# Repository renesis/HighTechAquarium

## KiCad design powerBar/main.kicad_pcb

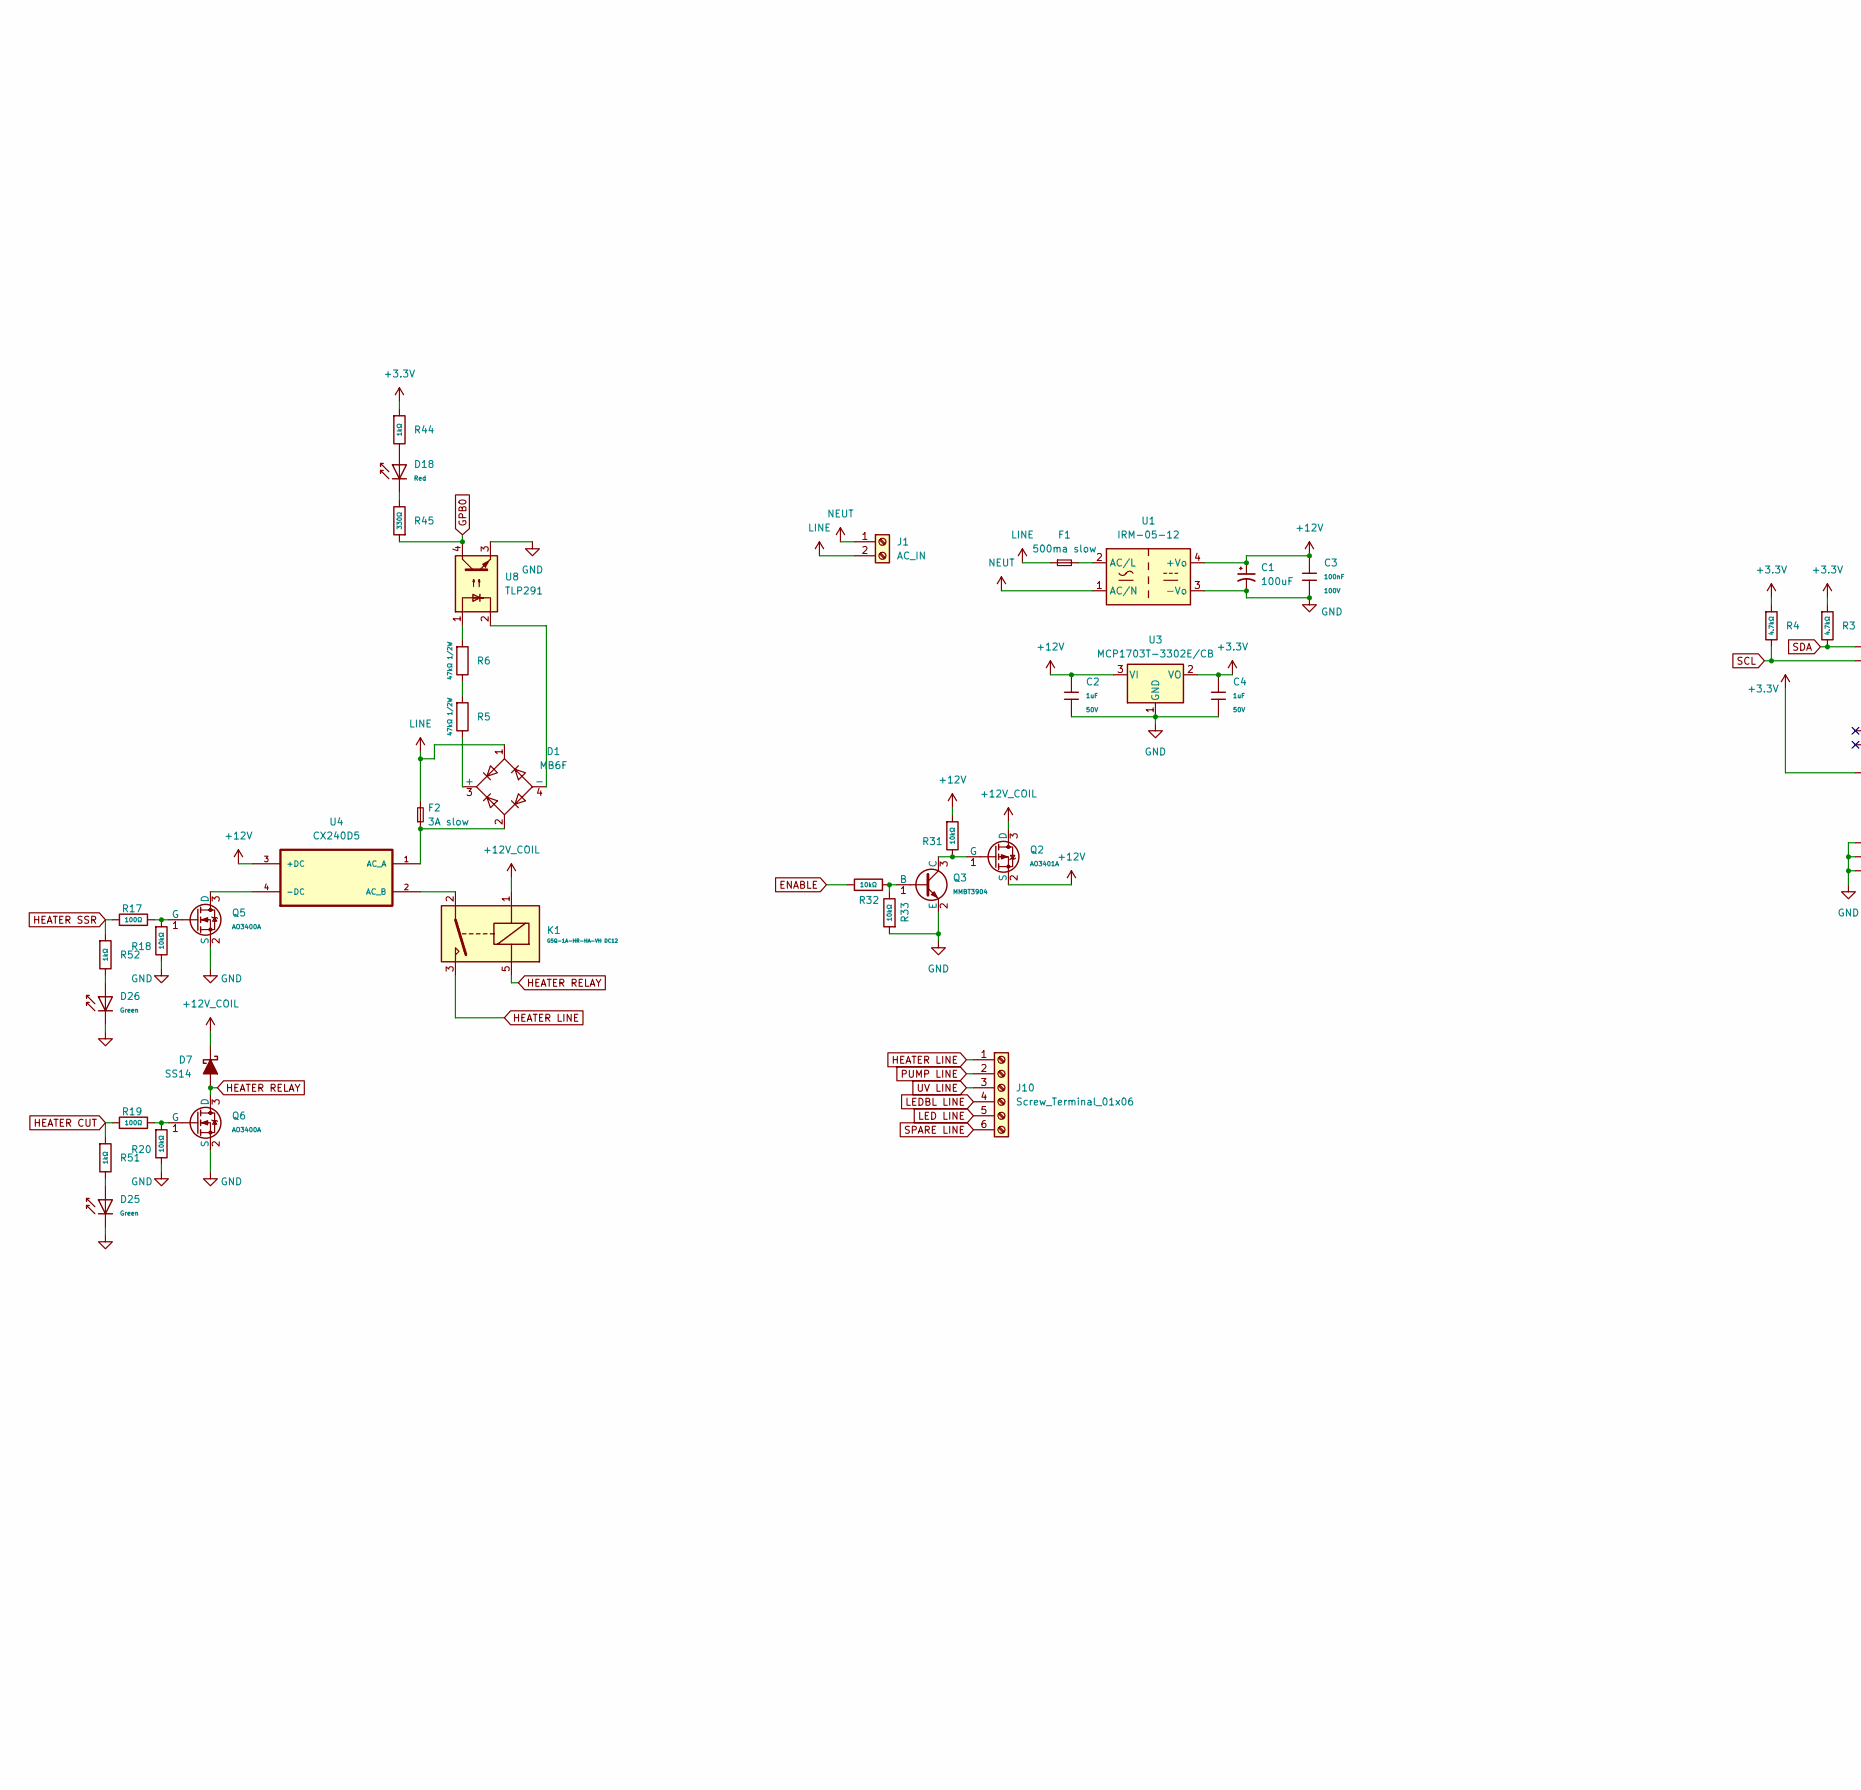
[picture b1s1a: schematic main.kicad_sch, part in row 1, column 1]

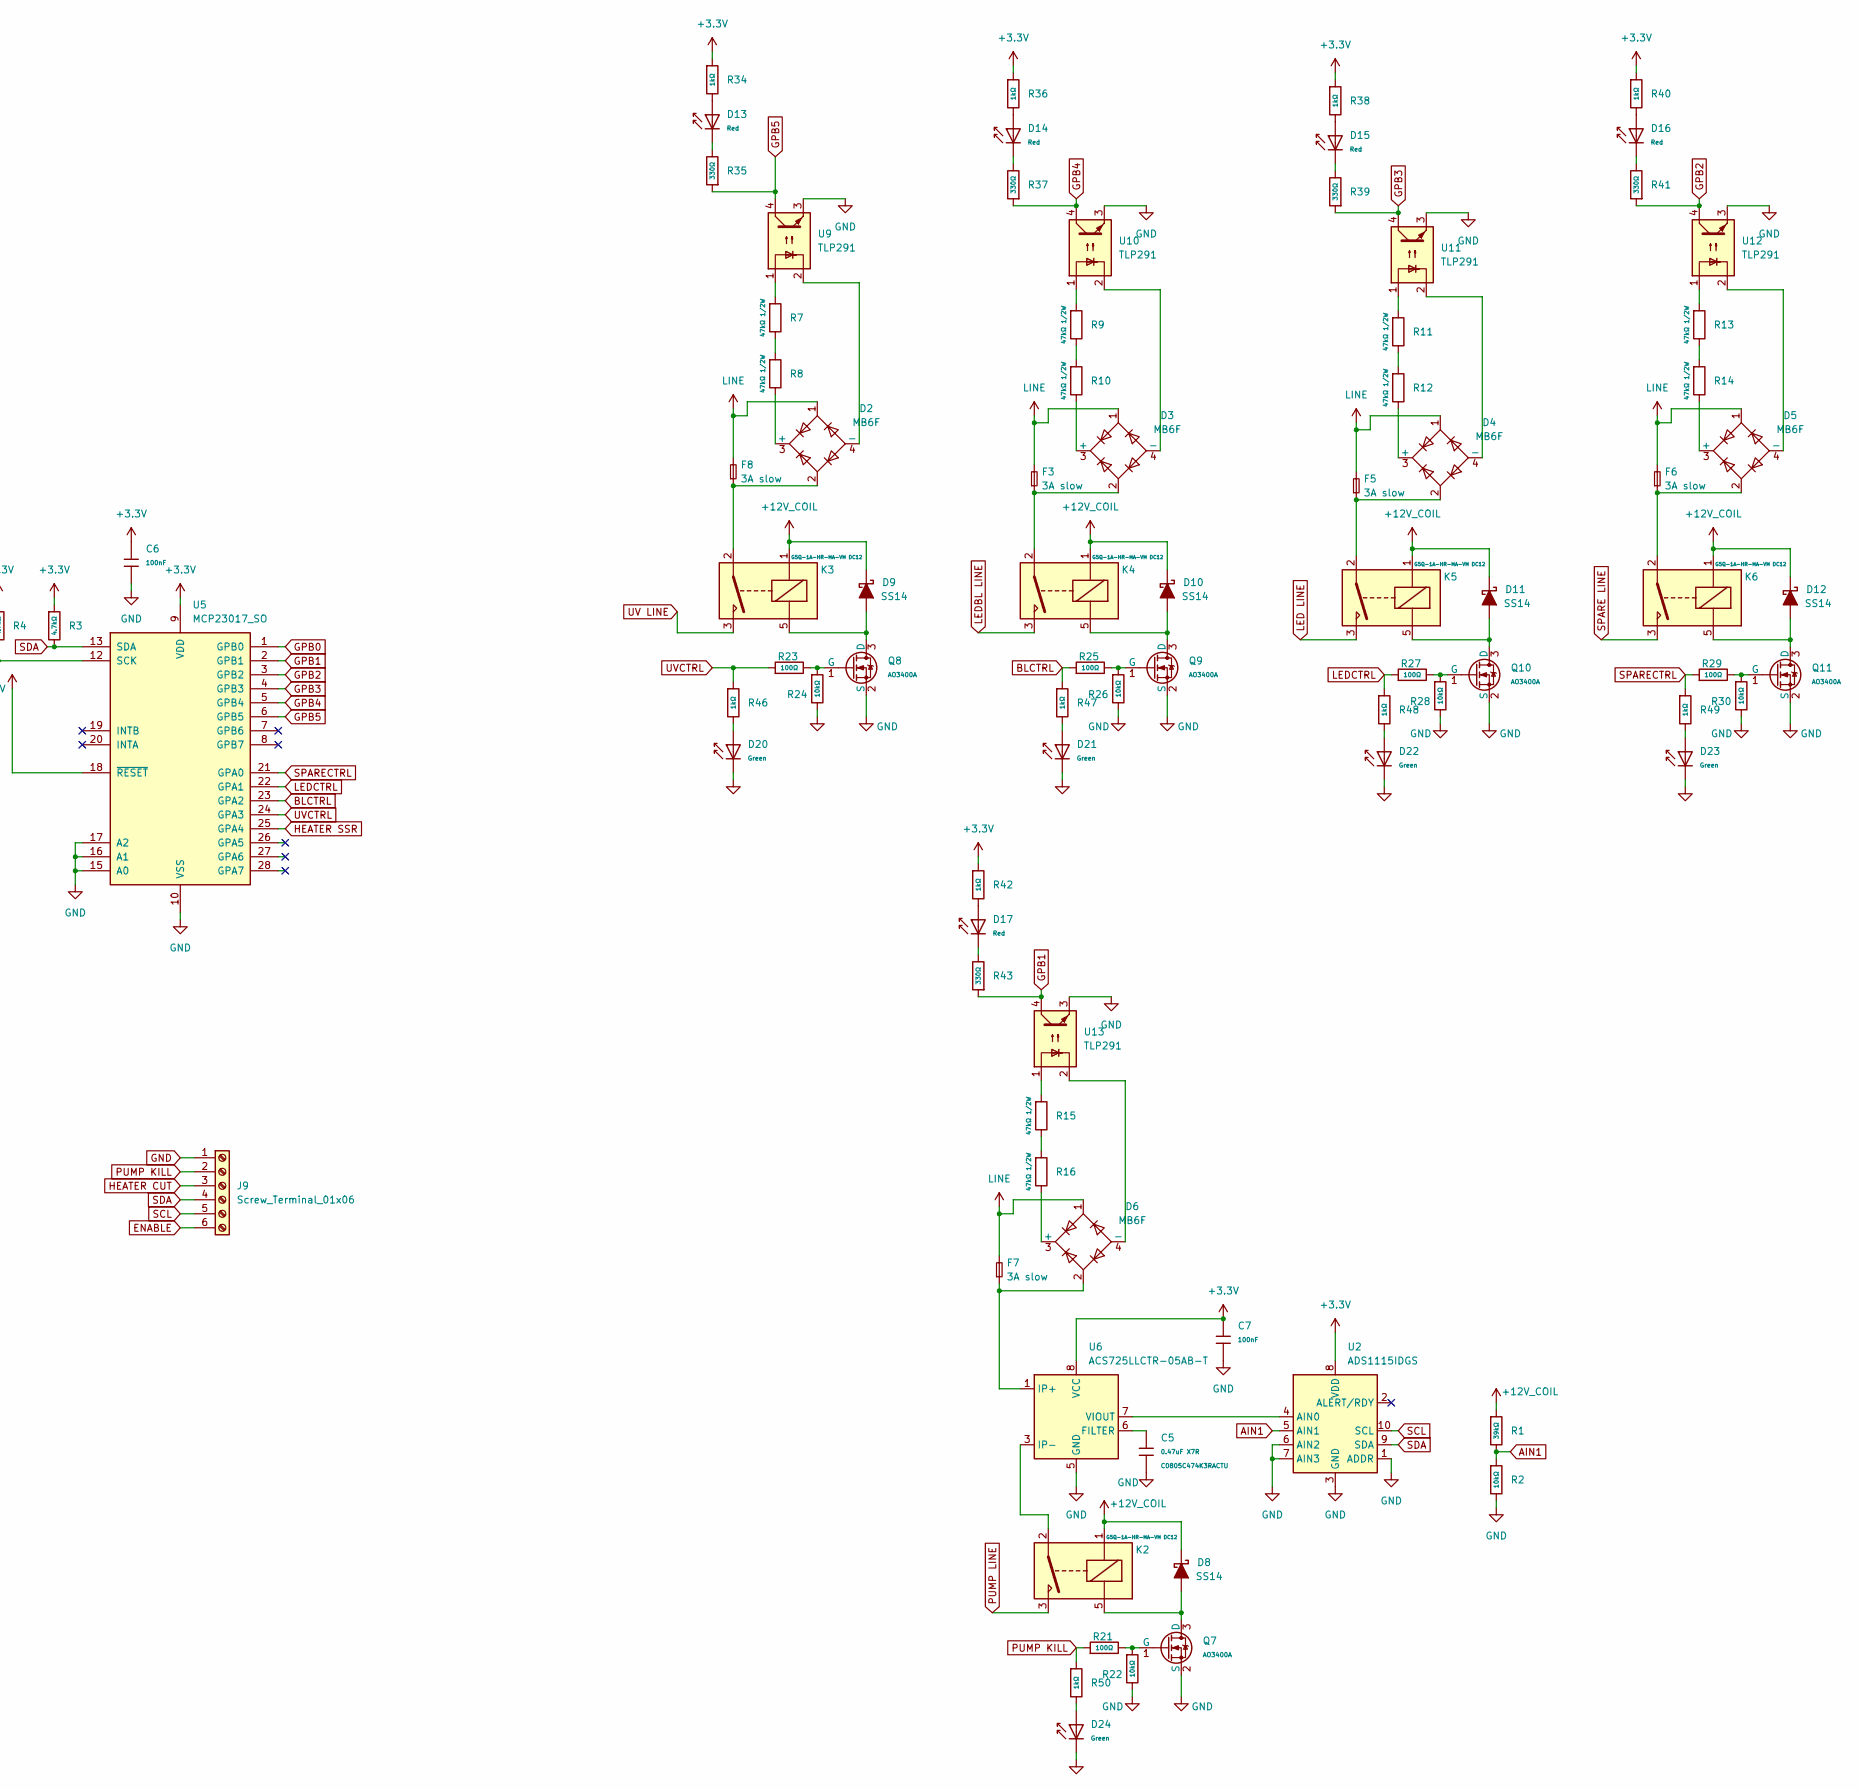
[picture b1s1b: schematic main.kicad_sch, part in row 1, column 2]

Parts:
C1: 100uF; C_Radial_D6.3mm_H11.0mm_P2.50mm
C2, C4: 1uF; C_0805; Voltage Rated 50V; Tolerance ±10%; Part CL21B105KBFNNNE; LCSC C28323
C3: 100nF; C_0805; Voltage Rated 100V; Tolerance ±10%; Part CL21B104KCFNNNE; LCSC C28233
C5: 0.47uF X7R; C_0805; Voltage Rated C0805C474K3RACTU; Tolerance ±10%; Part CL21B105KBFNNNE
C6, C7: 100nF; C_0805; Voltage Rated 50V; Tolerance ±10%; Part CC0805KRX7R9BB104; LCSC C49678
D1, D2, D3, D4, D5, D6: MB6F; TO-269AA
D7, D8, D9, D10, D11, D12: SS14; D_SMA
D13, D14, D15, D16, D17, D18: Red; D_0805; Forward Voltage (VF) 1.6V~2.6V; Part NCD0805R1; LCSC C84256
D20, D21, D22, D23, D24, D25, D26: Green; D_0805; Part KT-0805G; LCSC C2297
F1: 500ma slow; Fuseholder_Blade_Mini_Keystone_3568
F2, F3, F5, F6, F7, F8: 3A slow; Fuseholder_Blade_Mini_Keystone_3568
J1: AC_IN; TerminalBlock_CUI_TB007-508-02_1x02_P5.08mm_Horizontal
J9, J10: Screw_Terminal_01x06; TerminalBlock_CUI_TB007-508-06_1x06_P5.08mm_Horizontal
K1, K2, K3, K4, K5, K6: G5Q-1A-HR-HA-VH DC12; Relay_SPST_Omron-G5Q-1A
Q2: AO3401A; Q_SOT-23; Part AO3401A; LCSC C15127
Q3: MMBT3904; Q_SOT-23; Part MMBT3904; LCSC C7420353
Q5, Q6, Q7, Q8, Q9, Q10, Q11: AO3400A; Q_SOT-23; Part AO3400A; LCSC C20917
R1: 39kΩ; R_0805; Overload Voltage (Max) 150V; Tolerance ±1%; Part 0805W8F3902T5E; LCSC C25826
R2, R18, R20, R22, R24, R26, R28, R30, R31, R32, R33: 10kΩ; R_0805; Overload Voltage (Max) 150V; Tolerance ±1%; Part 0805W8F1002T5E; LCSC C17414
R3, R4: 4.7kΩ; R_0805; Overload Voltage (Max) 150V; Tolerance ±1%; Part 0805W8F4701T5E; LCSC C17673
R5, R6, R7, R8, R9, R10, R11, R12, R13, R14, R15, R16: 47kΩ 1/2W; R_0805; Overload Voltage (Max) 150V; Tolerance ±1%; Part 0805W8F4702T5E
R17, R19, R21, R23, R25, R27, R29: 100Ω; R_0805; Overload Voltage (Max) 150V; Tolerance ±1%; Part 0805W8F1000T5E; LCSC C17408
R34, R36, R38, R40, R42, R44, R46, R47, R48, R49, R50, R51, R52: 1kΩ; R_0805; Overload Voltage (Max) 150V; Tolerance ±1%; Part 0805W8F1001T5E; LCSC C17513
R35, R37, R39, R41, R43, R45: 330Ω; R_0805; Overload Voltage (Max) 150V; Tolerance ±1%; Part 0805W8F3300T5E; LCSC C17630
U1: IRM-05-12; Converter_ACDC_MeanWell_IRM-05-xx_THT
U2: ADS1115IDGS; TSSOP-10_3x3mm_P0.5mm
U3: MCP1703T-3302E/CB; SOT-23
U4: CX240D5; CRYDOM_CX240D5
U5: MCP23017_SO; SOIC-28W_7.5x17.9mm_P1.27mm
U6: ACS725LLCTR-05AB-T; SOIC-8_3.9x4.9mm_P1.27mm
U8, U9, U10, U11, U12, U13: TLP291; SOIC-4_4.55x2.6mm_P1.27mm

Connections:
+3.3V: C4.1, C6.1, C7.1, R3.1, R4.1, R34.1, R36.1, R38.1, R40.1, R42.1, R44.1, U2.8 (VDD), U3.2 (VO), U5.9 (VDD), U5.18 (~RESET), U6.8 (VCC)
+12V: C1.1, C2.1, C3.1, Q2.2 (S), R31.1, U1.4 (+Vo), U3.3 (VI), U4.3 (+DC)
+12V_COIL: D7.1 (K), D8.1 (K), D9.1 (K), D10.1 (K), D11.1 (K), D12.1 (K), K1.1, K2.1, K3.1, K4.1, K5.1, K6.1, Q2.3 (D), R1.1
AIN1: R1.2, R2.1, U2.5 (AIN1)
BLCTRL: R25.1, R47.1, U5.23 (GPA2)
ENABLE: J9.6, R32.1
GND: C1.2, C2.2, C3.2, C4.2, C5.2, C6.2, C7.2, D20.1, D21.1, D22.1, D23.1, D24.1, D25.1, D26.1, J9.1, Q3.2 (E), Q5.2 (S), Q6.2 (S), Q7.2 (S), Q8.2 (S), Q9.2 (S), Q10.2 (S), Q11.2 (S), R2.2, R18.2, R20.2, R22.2, R24.2, R26.2, R28.2, R30.2, R33.1, U1.3 (-Vo), U2.1 (ADDR), U2.3 (GND), U2.6 (AIN2), U2.7 (AIN3), U3.1 (GND), U5.10 (VSS), U5.15 (A0), U5.16 (A1), U5.17 (A2), U6.5 (GND), U8.3, U9.3, U10.3, U11.3, U12.3, U13.3
GPB0: R45.1, U5.1 (GPB0), U8.4
GPB1: R43.1, U5.2 (GPB1), U13.4
GPB2: R41.1, U5.3 (GPB2), U12.4
GPB3: R39.1, U5.4 (GPB3), U11.4
GPB4: R37.1, U5.5 (GPB4), U10.4
GPB5: R35.1, U5.6 (GPB5), U9.4
HEATER CUT: J9.3, R19.1, R51.1
HEATER LINE: J10.1, K1.3
HEATER RELAY: D7.2 (A), K1.5, Q6.3 (D)
HEATER SSR: R17.1, R52.1, U5.25 (GPA4)
LED LINE: J10.5, K5.3
LEDBL LINE: J10.4, K4.3
LEDCTRL: R27.1, R48.1, U5.22 (GPA1)
LINE: D1.1, D2.1, D3.1, D4.1, D5.1, D6.1, F1.1, F2.2, F3.2, F5.2, F6.2, F7.2, F8.2, J1.2
NEUT: J1.1, U1.1 (AC/N)
unnamed: D1.3 (+), R5.2
unnamed: D1.4 (-), U8.2
unnamed: D2.3 (+), R8.2
unnamed: D2.4 (-), U9.2
unnamed: D2.2, F8.1, K3.2
unnamed: D3.3 (+), R10.2
unnamed: D3.4 (-), U10.2
unnamed: D3.2, F3.1, K4.2
unnamed: D4.3 (+), R12.2
unnamed: D4.4 (-), U11.2
unnamed: D4.2, F5.1, K5.2
unnamed: D5.3 (+), R14.2
unnamed: D5.4 (-), U12.2
unnamed: D5.2, F6.1, K6.2
unnamed: D6.3 (+), R16.2
unnamed: D6.4 (-), U13.2
unnamed: D6.2, F7.1, U6.1 (IP+), U6.2 (IP+)
unnamed: D8.2 (A), K2.5, Q7.3 (D)
unnamed: D9.2 (A), K3.5, Q8.3 (D)
unnamed: D10.2 (A), K4.5, Q9.3 (D)
unnamed: D11.2 (A), K5.5, Q10.3 (D)
unnamed: D12.2 (A), K6.5, Q11.3 (D)
unnamed: D13.1, R35.2
unnamed: D13.2, R34.2
unnamed: D14.1, R37.2
unnamed: D14.2, R36.2
unnamed: D15.1, R39.2
unnamed: D15.2, R38.2
unnamed: D16.1, R41.2
unnamed: D16.2, R40.2
unnamed: D17.1, R43.2
unnamed: D17.2, R42.2
unnamed: D18.1, R45.2
unnamed: D18.2, R44.2
unnamed: D20.2, R46.2
unnamed: D21.2, R47.2
unnamed: D22.2, R48.2
unnamed: D23.2, R49.2
unnamed: D24.2, R50.2
unnamed: D25.2, R51.2
unnamed: D26.2, R52.2
unnamed: K2.2, U6.3 (IP-), U6.4 (IP-)
unnamed: Q2.1 (G), Q3.3 (C), R31.2
unnamed: Q3.1 (B), R32.2, R33.2
unnamed: Q5.3 (D), U4.4 (-DC)
unnamed: Q5.1 (G), R17.2, R18.1
unnamed: Q6.1 (G), R19.2, R20.1
unnamed: Q7.1 (G), R21.2, R22.1
unnamed: Q8.1 (G), R23.2, R24.1
unnamed: Q9.1 (G), R25.2, R26.1
unnamed: Q10.1 (G), R27.2, R28.1
unnamed: Q11.1 (G), R29.2, R30.1
unnamed: R5.1, R6.2
unnamed: R6.1, U8.1
unnamed: R7.1, U9.1
unnamed: R7.2, R8.1
unnamed: R9.1, U10.1
unnamed: R9.2, R10.1
unnamed: R11.1, U11.1
unnamed: R11.2, R12.1
unnamed: R13.1, U12.1
unnamed: R13.2, R14.1
unnamed: R15.1, U13.1
unnamed: R15.2, R16.1
unnamed: F1.2, U1.2 (AC/L)
unnamed: U2.4 (AIN0), U6.7 (VIOUT)
unnamed: D1.2, F2.1, U4.1 (AC_A)
unnamed: K1.2, U4.2 (AC_B)
unnamed: C5.1, U6.6 (FILTER)
PUMP KILL: J9.2, R21.1, R50.1
PUMP LINE: J10.2, K2.3
SCL: J9.5, R4.2, U2.10 (SCL), U5.12 (SCK)
SDA: J9.4, R3.2, U2.9 (SDA), U5.13 (SDA)
SPARE LINE: J10.6, K6.3
SPARECTRL: R29.1, R49.1, U5.21 (GPA0)
UV LINE: J10.3, K3.3
UVCTRL: R23.1, R46.1, U5.24 (GPA3)

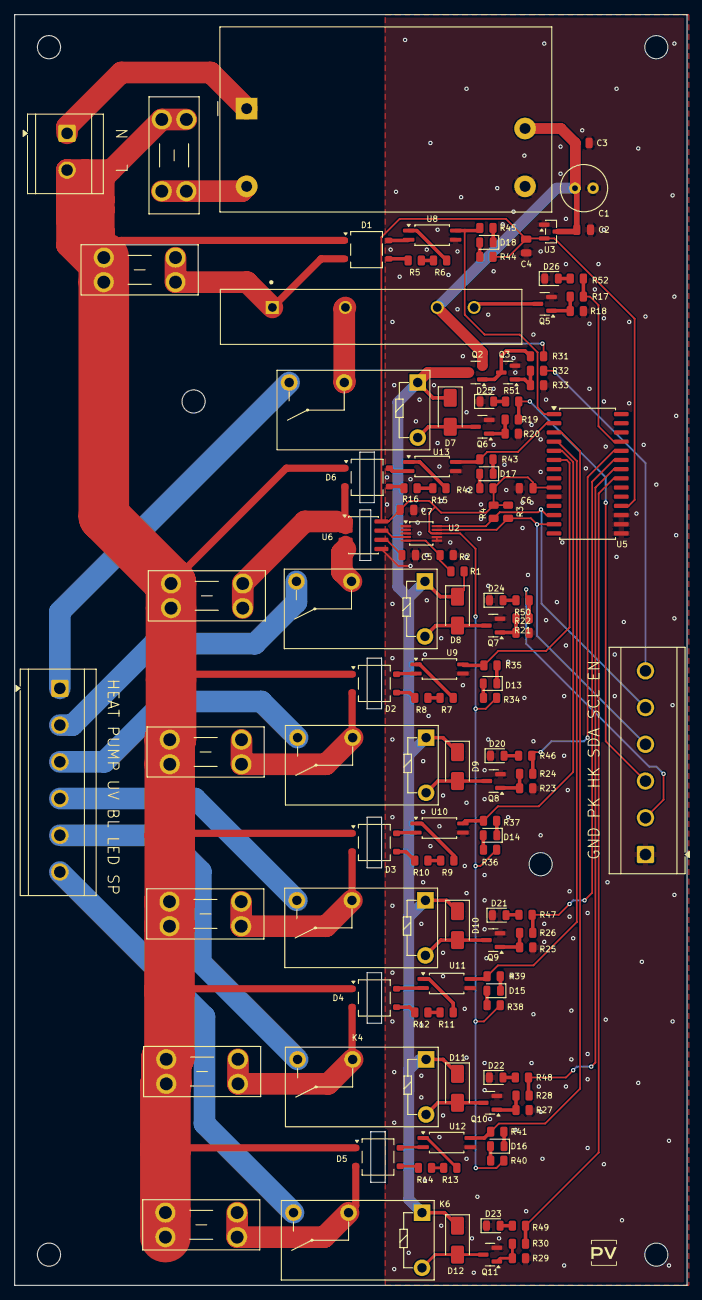
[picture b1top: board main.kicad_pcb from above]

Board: 2 copper layers, 93.0 x 175.8 mm, 121 parts (0 on the bottom side), 99 nets.

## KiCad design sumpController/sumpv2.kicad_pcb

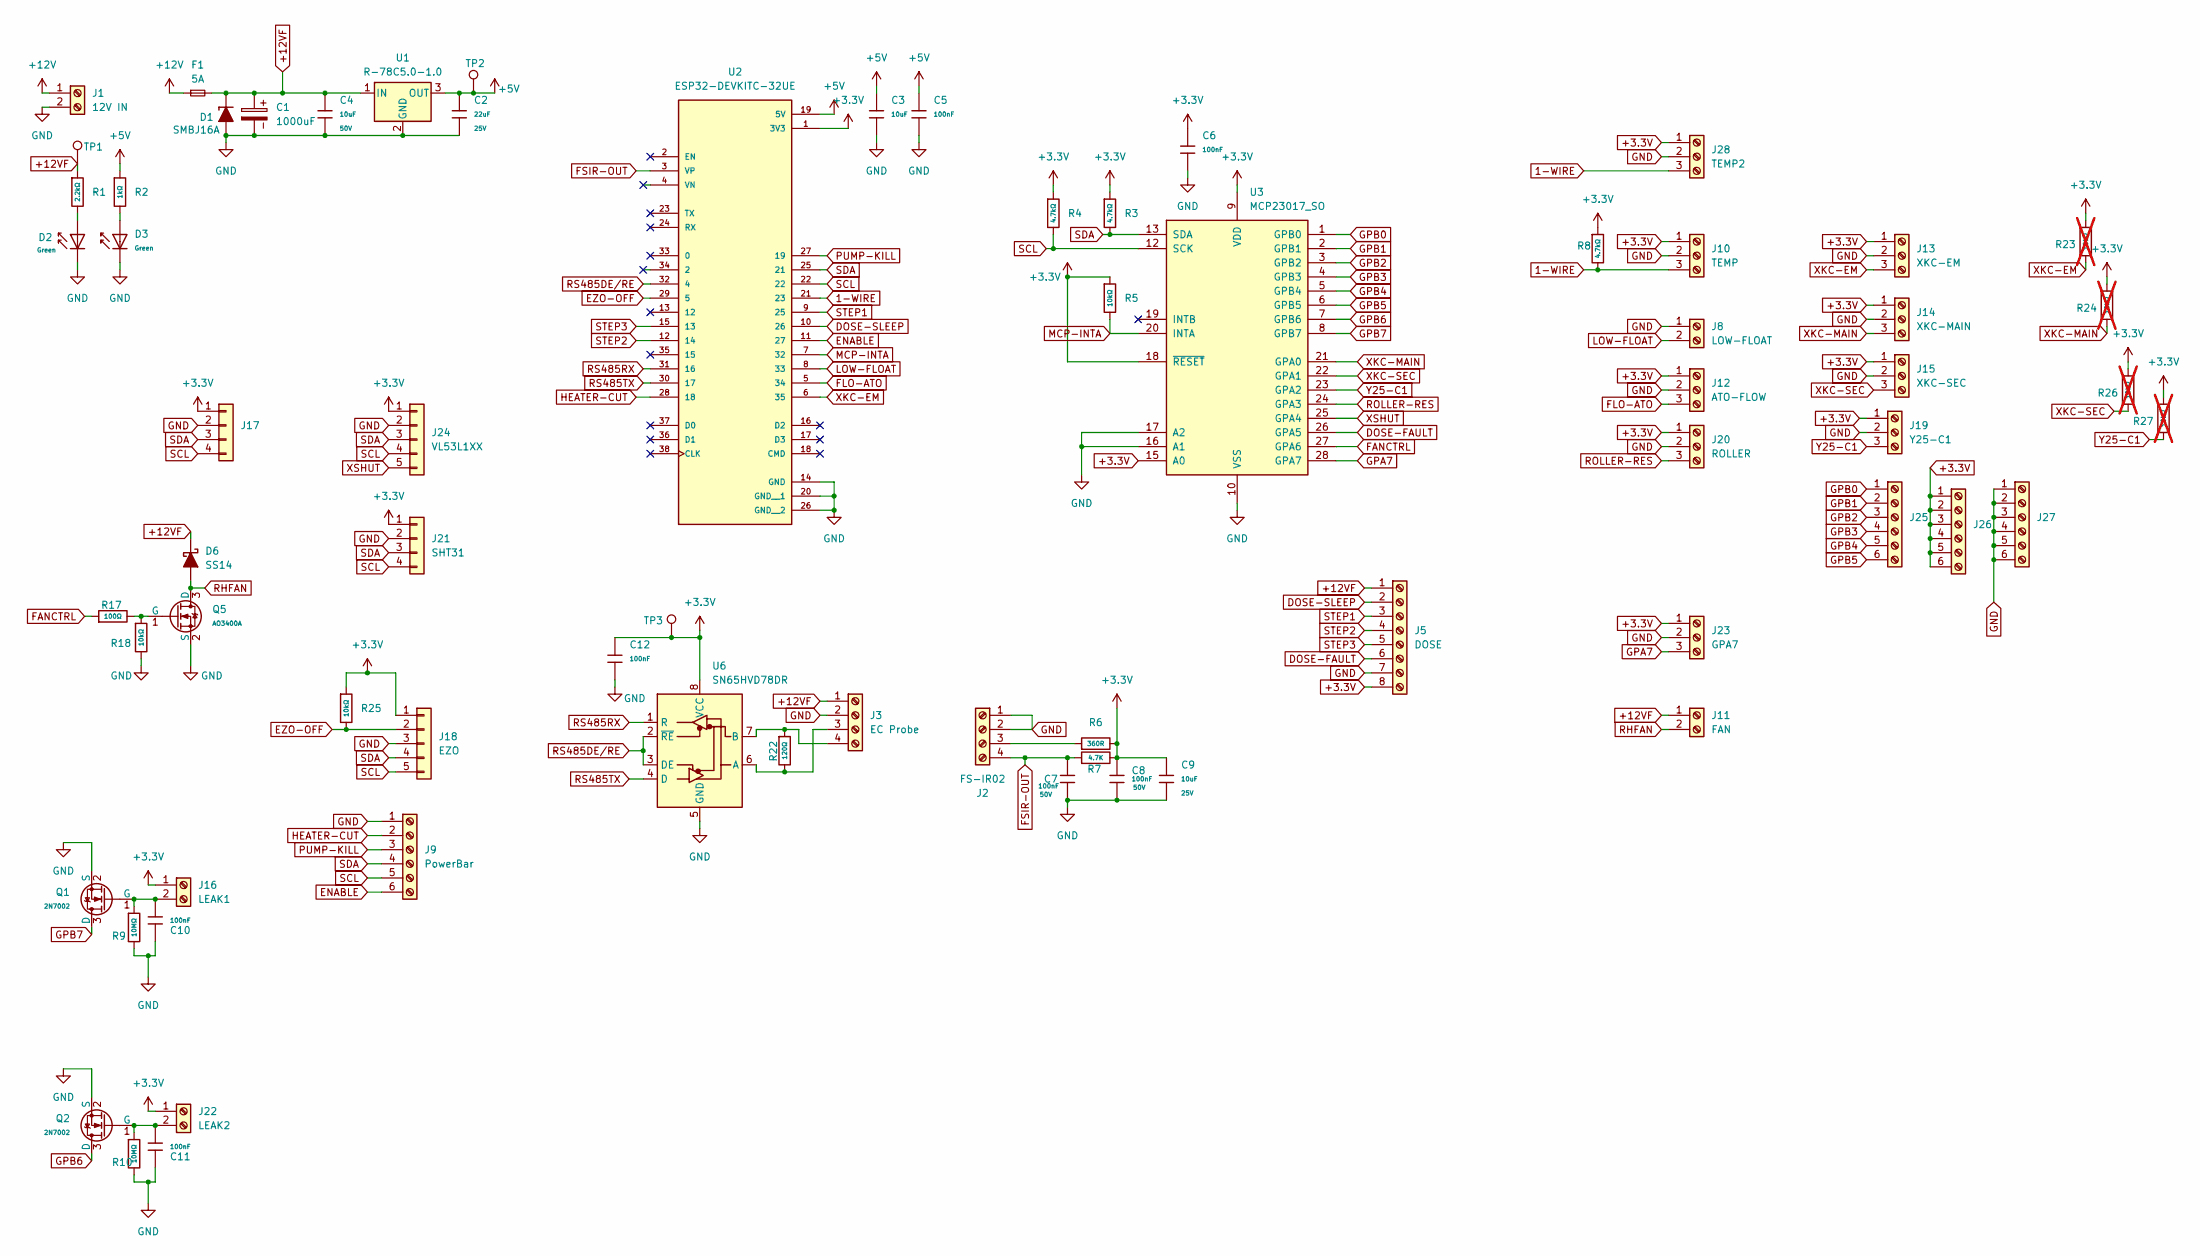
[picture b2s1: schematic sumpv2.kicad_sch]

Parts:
C1: 1000uF; CP_Radial_D13.0mm_P5.00mm
C2: 22uF; C_0805; Voltage Rated 25V; Tolerance ±20%; Part CL21A226MAQNNNE; LCSC C45783
C3, C9: 10uF; C_0805; Voltage Rated 25V; Tolerance ±10%; Part CL21A106KAYNNNE; LCSC C15850
C4: 10uF; C_1206; Voltage Rated 50V; Tolerance ±10%; Part CL31A106KBHNNNE; LCSC C13585
C5, C6, C7, C8, C10, C11, C12: 100nF; C_0805; Voltage Rated 50V; Tolerance ±10%; Part CC0805KRX7R9BB104; LCSC C49678
D1: SMBJ16A; D_SMB
D2, D3: Green; D_0805; Part KT-0805G; LCSC C2297
D6: SS14; D_SMA
F1: 5A; Fuseholder_Blade_Mini_Keystone_3568
J1: 12V IN; TerminalBlock_CUI_TB007-508-02_1x02_P5.08mm_Horizontal
J2: FS-IR02; JST_XH_B4B-XH-A_1x04_P2.50mm_Vertical
J3: EC Probe; JST_XH_B4B-XH-A_1x04_P2.50mm_Vertical
J5: DOSE; TerminalBlock_Phoenix_MPT-0,5-8-2.54_1x08_P2.54mm_Horizontal
J8: LOW-FLOAT; JST_XH_B2B-XH-A_1x02_P2.50mm_Vertical
J9: PowerBar; TerminalBlock_Phoenix_MPT-0,5-6-2.54_1x06_P2.54mm_Horizontal
J10: TEMP; JST_XH_B3B-XH-A_1x03_P2.50mm_Vertical
J11: FAN; JST_XH_B2B-XH-A_1x02_P2.50mm_Vertical
J12: ATO-FLOW; JST_XH_B3B-XH-A_1x03_P2.50mm_Vertical
J13: XKC-EM; JST_XH_B3B-XH-A_1x03_P2.50mm_Vertical
J14: XKC-MAIN; JST_XH_B3B-XH-A_1x03_P2.50mm_Vertical
J15: XKC-SEC; JST_XH_B3B-XH-A_1x03_P2.50mm_Vertical
J16: LEAK1; JST_XH_B2B-XH-A_1x02_P2.50mm_Vertical
J17: Conn_01x04; PinHeader_1x04_P1.27mm_Vertical
J18: EZO; TerminalBlock_Phoenix_MPT-0,5-5-2.54_1x05_P2.54mm_Horizontal
J19: Y25-C1; JST_XH_B3B-XH-A_1x03_P2.50mm_Vertical
J20: ROLLER; JST_XH_B3B-XH-A_1x03_P2.50mm_Vertical
J21: SHT31; JST_XH_B4B-XH-A_1x04_P2.50mm_Vertical
J22: LEAK2; JST_XH_B2B-XH-A_1x02_P2.50mm_Vertical
J23: GPA7; JST_XH_B3B-XH-A_1x03_P2.50mm_Vertical
J24: VL53L1XX; TerminalBlock_Phoenix_MPT-0,5-5-2.54_1x05_P2.54mm_Horizontal
J25, J26, J27: Screw_Terminal_01x06; PinHeader_1x06_P2.00mm_Vertical
J28: TEMP2; JST_XH_B3B-XH-A_1x03_P2.50mm_Vertical
Q1, Q2: 2N7002; Q_SOT-23; Part 2N7002; LCSC C8545
Q5: AO3400A; Q_SOT-23; Part AO3400A; LCSC C20917
R1: 2.2kΩ; R_0805; Overload Voltage (Max) 150V; Tolerance ±1%; Part 0805W8F2201T5E; LCSC C17520
R2: 1kΩ; R_0805; Overload Voltage (Max) 150V; Tolerance ±1%; Part 0805W8F1001T5E; LCSC C17513
R3, R4, R8: 4.7kΩ; R_0805; Overload Voltage (Max) 150V; Tolerance ±1%; Part 0805W8F4701T5E; LCSC C17673
R5, R18, R25: 10kΩ; R_0805; Overload Voltage (Max) 150V; Tolerance ±1%; Part 0805W8F1002T5E; LCSC C17414
R6: 360R; R_0805; Overload Voltage (Max) 150V; Tolerance ±1%
R7: 4.7K; R_0805; Overload Voltage (Max) 150V; Tolerance ±1%
R9, R10: 10MΩ; R_0805; Overload Voltage (Max) 150V; Tolerance ±1%; Part 0805W8F1005T5E; LCSC C26108
R17: 100Ω; R_0805; Overload Voltage (Max) 150V; Tolerance ±1%; Part 0805W8F1000T5E; LCSC C17408
R22: 120Ω; R_0805; Overload Voltage (Max) 150V; Tolerance ±1%; Part 0805W8F1200T5E; LCSC C17437
R23, R24, R26, R27: 10kΩ; R_0805; Overload Voltage (Max) 150V; Tolerance ±1%; Part 0805W8F1002T5E; LCSC C17414; not fitted
TP1, TP2, TP3: TestPoint; TestPoint_Pad_1.0x1.0mm
U1: R-78C5.0-1.0; Converter_DCDC_RECOM_R-78E-0.5_THT
U2: ESP32-DEVKITC-32UE; ESPRESSIF_ESP32-DEVKITC-32UE; PARTREV V4
U3: MCP23017_SO; SOIC-28W_7.5x17.9mm_P1.27mm
U6: SN65HVD78DR; SOIC-8_3.9x4.9mm_P1.27mm

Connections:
1-WIRE: J10.3, J28.3, R8.2, U2.21 (23)
+3.3V: C6.1, C8.1, C9.1, C12.1, J5.8, J10.1, J12.1, J13.1, J14.1, J15.1, J16.1, J17.1, J18.1, J19.1, J20.1, J21.1, J22.1, J23.1, J24.1, J26.1, J26.2, J26.3, J26.4, J26.5, J26.6, J28.1, R3.1, R4.1, R5.1, R6.2, R7.2, R8.1, R23.1, R24.1, R25.1, R26.1, R27.1, TP3.1 (1_1), U2.1 (3V3), U3.9 (VDD), U3.15 (A0), U3.18 (~RESET), U6.8 (VCC)
+5V: C2.1, C3.1, C5.1, R2.1, TP2.1 (1_1), U1.3 (OUT), U2.19 (5V)
+12V: F1.1, J1.1
+12VF: C1.1, C4.1, D1.1 (K), D6.1 (K), F1.2, J3.1, J5.1, J11.1, R1.1, TP1.1 (1_1), U1.1 (IN)
DOSE-FAULT: J5.6, U3.26 (GPA5)
DOSE-SLEEP: J5.2, U2.10 (26)
ENABLE: J9.6, U2.11 (27)
EZO-OFF: J18.2, R25.2, U2.29 (5)
FANCTRL: R17.1, U3.27 (GPA6)
FLO-ATO: J12.3, U2.5 (34)
FSIR-OUT: C7.1, J2.4, R7.1, U2.3 (VP)
GND: C1.2, C2.2, C3.2, C4.2, C5.2, C6.2, C7.2, C8.2, C9.2, C10.2, C11.2, C12.2, D1.2 (A), D2.1, D3.1, J1.2, J2.1, J2.2, J3.2, J5.7, J8.1, J9.1, J10.2, J12.2, J13.2, J14.2, J15.2, J17.2, J18.3, J19.2, J20.2, J21.2, J23.2, J24.2, J27.1, J27.2, J27.3, J27.4, J27.5, J27.6, J28.2, Q1.2 (S), Q2.2 (S), Q5.2 (S), R9.2, R10.2, R18.2, U1.2 (GND), U2.14 (GND), U2.20 (GND__1), U2.26 (GND__2), U3.10 (VSS), U3.16 (A1), U3.17 (A2), U6.5 (GND)
GPA7: J23.3, U3.28 (GPA7)
GPB0: J25.1, U3.1 (GPB0)
GPB1: J25.2, U3.2 (GPB1)
GPB2: J25.3, U3.3 (GPB2)
GPB3: J25.4, U3.4 (GPB3)
GPB4: J25.5, U3.5 (GPB4)
GPB5: J25.6, U3.6 (GPB5)
GPB6: Q2.3 (D), U3.7 (GPB6)
GPB7: Q1.3 (D), U3.8 (GPB7)
HEATER-CUT: J9.2, U2.28 (18)
LOW-FLOAT: J8.2, U2.8 (33)
MCP-INTA: R5.2, U2.7 (32), U3.20 (INTA)
unnamed: D2.2, R1.2
unnamed: D3.2, R2.2
unnamed: J2.3, R6.1
unnamed: J3.3, R22.2, U6.6 (A)
unnamed: J3.4, R22.1, U6.7 (B)
unnamed: C10.1, J16.2, Q1.1 (G), R9.1
unnamed: C11.1, J22.2, Q2.1 (G), R10.1
unnamed: Q5.1 (G), R17.2, R18.1
PUMP-KILL: J9.3, U2.27 (19)
RHFAN: D6.2 (A), J11.2, Q5.3 (D)
ROLLER-RES: J20.3, U3.24 (GPA3)
RS485DE/RE: U2.32 (4), U6.2 (~RE), U6.3 (DE)
RS485RX: U2.31 (16), U6.1 (R)
RS485TX: U2.30 (17), U6.4 (D)
SCL: J9.5, J17.4, J18.5, J21.4, J24.4, R4.2, U2.22, U3.12 (SCK)
SDA: J9.4, J17.3, J18.4, J21.3, J24.3, R3.2, U2.25 (21), U3.13 (SDA)
STEP1: J5.3, U2.9 (25)
STEP2: J5.4, U2.12 (14)
STEP3: J5.5, U2.15 (13)
XKC-EM: J13.3, R23.2, U2.6 (35)
XKC-MAIN: J14.3, R24.2, U3.21 (GPA0)
XKC-SEC: J15.3, R26.2, U3.22 (GPA1)
XSHUT: J24.5, U3.25 (GPA4)
Y25-C1: J19.3, R27.2, U3.23 (GPA2)

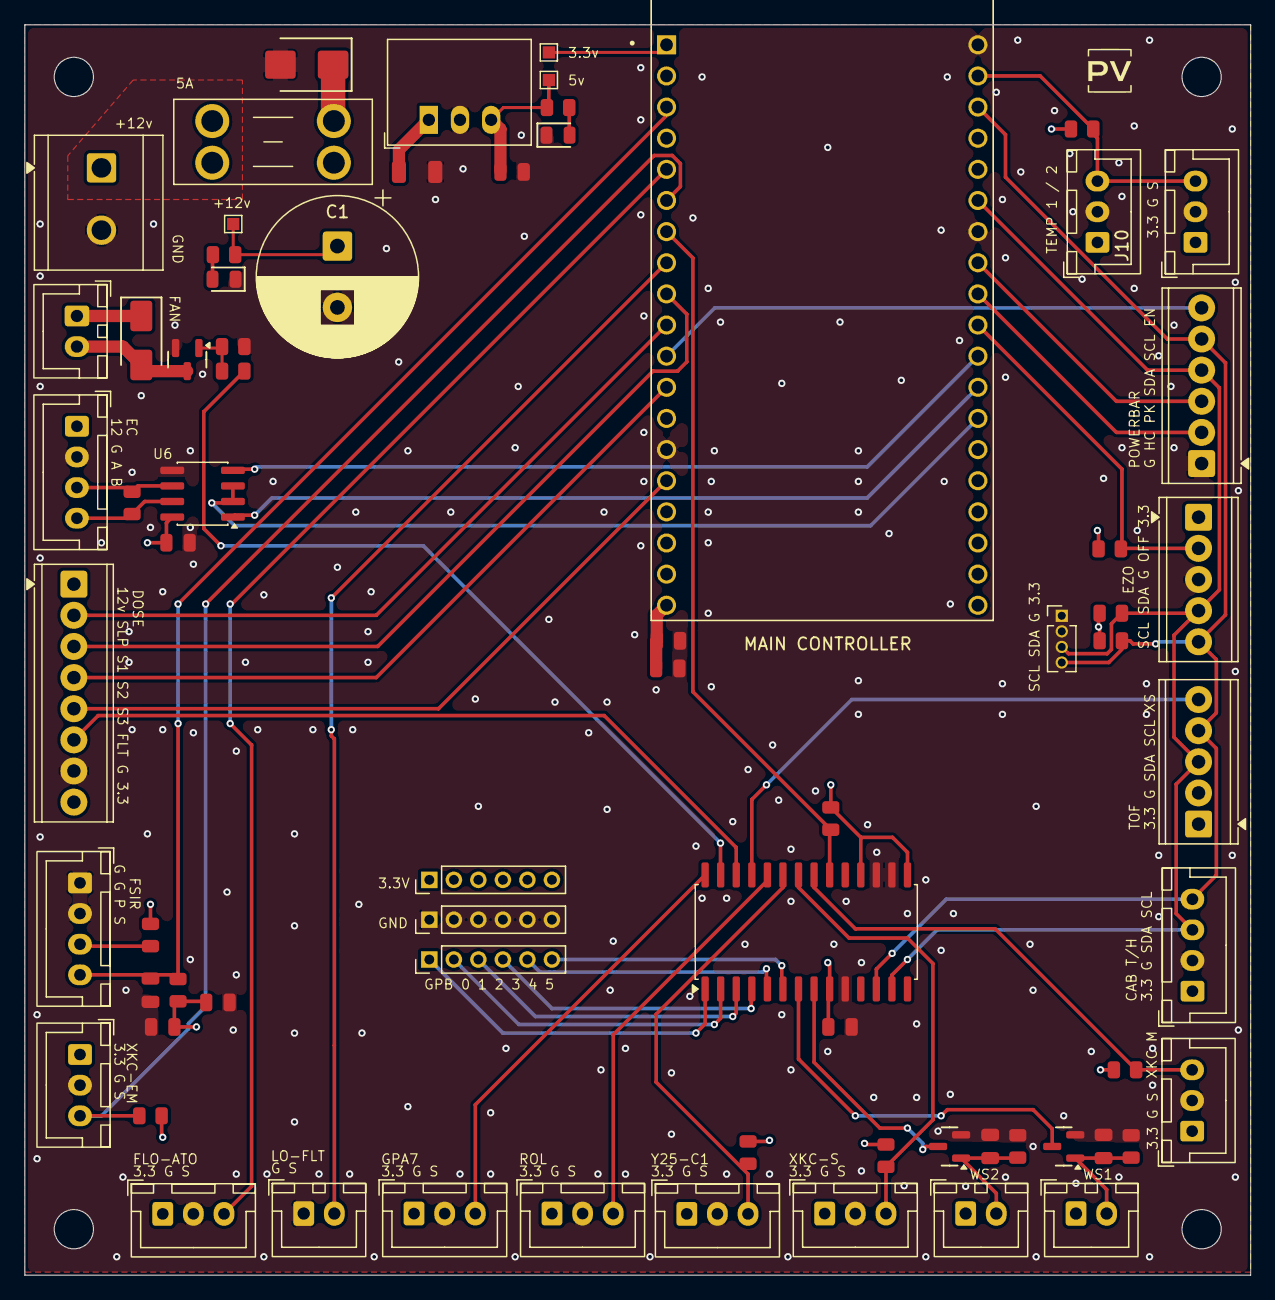
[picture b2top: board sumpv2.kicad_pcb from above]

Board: 4 copper layers, 100.0 x 102.0 mm, 70 parts (0 on the bottom side), 49 nets.

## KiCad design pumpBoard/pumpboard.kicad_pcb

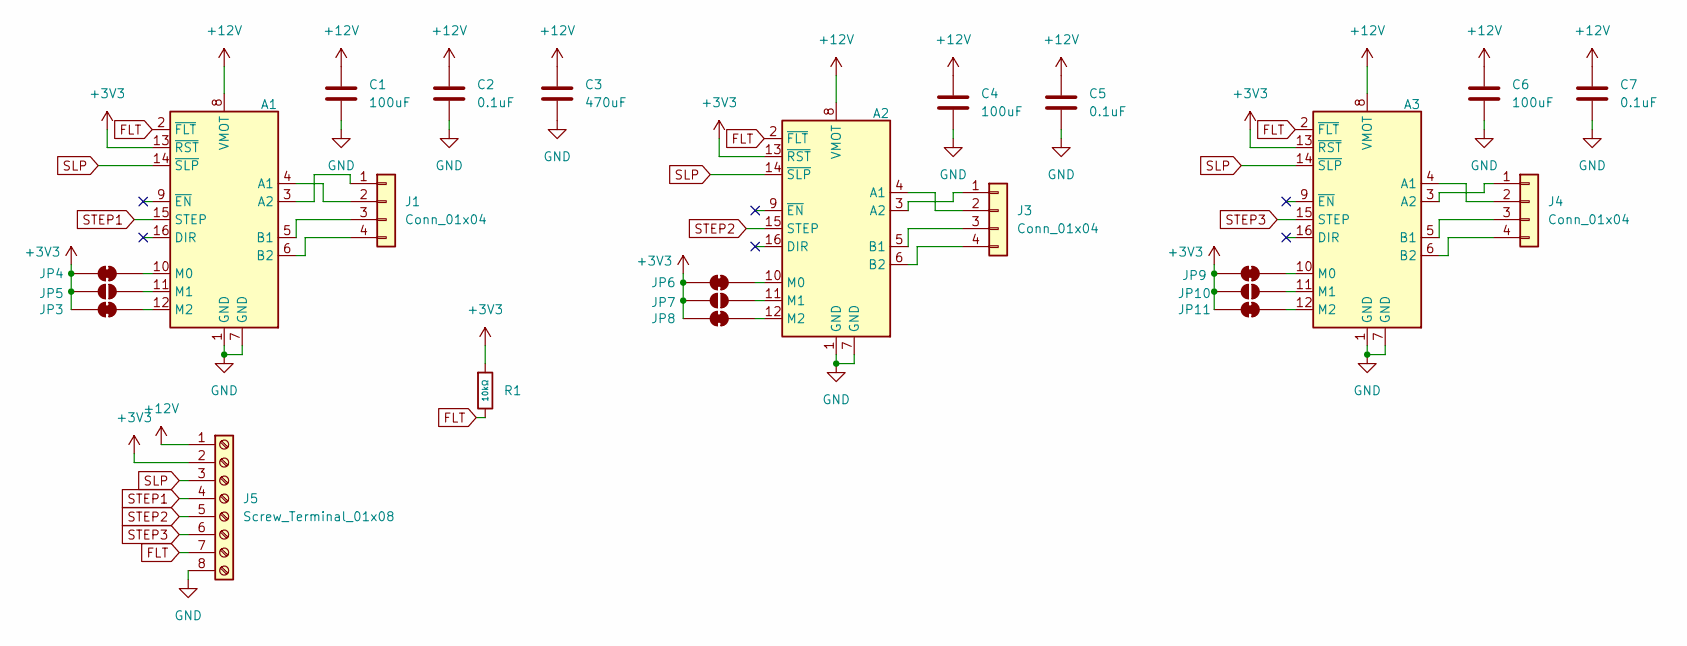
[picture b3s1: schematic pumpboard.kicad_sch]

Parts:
A1, A2, A3: Pololu_Breakout_DRV8825; Pololu_Breakout-16_15.2x20.3mm
C1, C4, C6: 100uF; CP_Radial_D6.3mm_P2.50mm
C2, C5, C7: 0.1uF; C_0805_2012Metric_Pad1.18x1.45mm_HandSolder
C3: 470uF; CP_Radial_D10.0mm_P5.00mm
J1, J3, J4: Conn_01x04; JST_XH_B4B-XH-A_1x04_P2.50mm_Vertical
J5: Screw_Terminal_01x08; TerminalBlock_Xinya_XY308-2.54-8P_1x08_P2.54mm_Horizontal
JP3, JP4, JP6, JP8, JP11: SolderJumper_2_Bridged; SolderJumper-2_P1.3mm_Bridged2Bar_Pad1.0x1.5mm
JP5, JP7, JP10: SolderJumper_2_Open; SolderJumper-2_P1.3mm_Open_Pad1.0x1.5mm
JP9: SolderJumper_2_Open; SolderJumper-2_P1.3mm_Bridged2Bar_Pad1.0x1.5mm
R1: 10kΩ; R_0805; Overload Voltage (Max) 150V; Tolerance ±1%; Part 0805W8F1002T5E; LCSC C17414

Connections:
+3V3: A1.13 (~RST), A2.13 (~RST), A3.13 (~RST), J5.2, JP3.1 (A), JP4.1 (A), JP5.1 (A), JP6.1 (A), JP7.1 (A), JP8.1 (A), JP9.1 (A), JP10.1 (A), JP11.1 (A), R1.1
+12V: A1.8 (VMOT), A2.8 (VMOT), A3.8 (VMOT), C1.1, C2.1, C3.1, C4.1, C5.1, C6.1, C7.1, J5.1
FLT: A1.2 (~FLT), A2.2 (~FLT), A3.2 (~FLT), J5.7, R1.2
GND: A1.1 (GND), A1.7 (GND), A2.1 (GND), A2.7 (GND), A3.1 (GND), A3.7 (GND), C1.2, C2.2, C3.2, C4.2, C5.2, C6.2, C7.2, J5.8
unnamed: A1.4 (A1), J1.2
unnamed: A1.3 (A2), J1.1
unnamed: A1.5 (B1), J1.3
unnamed: A1.6 (B2), J1.4
unnamed: A1.10 (M0), JP4.2 (B)
unnamed: A1.11 (M1), JP5.2 (B)
unnamed: A1.12 (M2), JP3.2 (B)
unnamed: A2.4 (A1), J3.2
unnamed: A2.3 (A2), J3.1
unnamed: A2.5 (B1), J3.3
unnamed: A2.6 (B2), J3.4
unnamed: A2.10 (M0), JP6.2 (B)
unnamed: A2.11 (M1), JP7.2 (B)
unnamed: A2.12 (M2), JP8.2 (B)
unnamed: A3.4 (A1), J4.2
unnamed: A3.3 (A2), J4.1
unnamed: A3.5 (B1), J4.3
unnamed: A3.6 (B2), J4.4
unnamed: A3.10 (M0), JP9.2 (B)
unnamed: A3.11 (M1), JP10.2 (B)
unnamed: A3.12 (M2), JP11.2 (B)
SLP: A1.14 (~SLP), A2.14 (~SLP), A3.14 (~SLP), J5.3
STEP1: A1.15 (STEP), J5.4
STEP2: A2.15 (STEP), J5.5
STEP3: A3.15 (STEP), J5.6

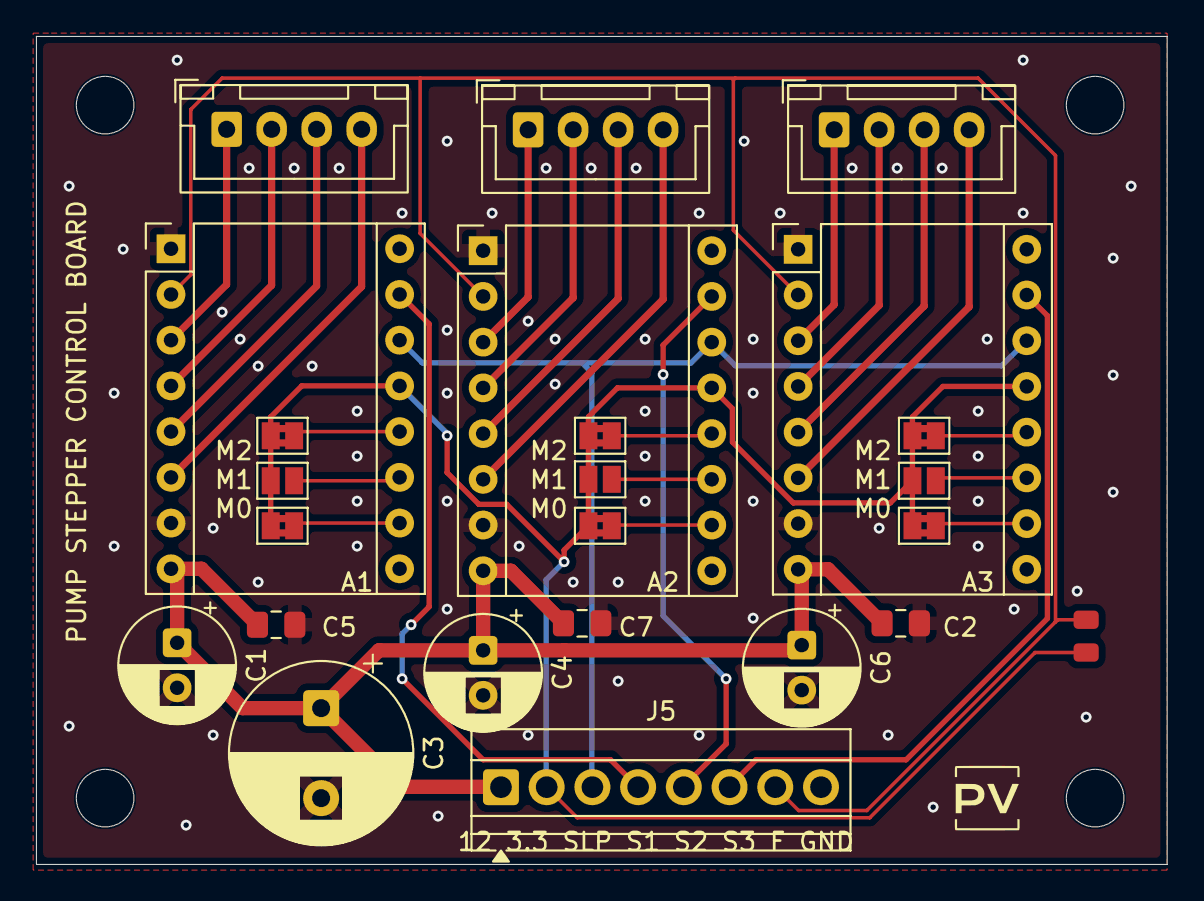
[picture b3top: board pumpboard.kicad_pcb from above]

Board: 2 copper layers, 62.8 x 46.0 mm, 24 parts (0 on the bottom side), 29 nets.
